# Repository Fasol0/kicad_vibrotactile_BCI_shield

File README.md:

## Printed Circuit board (PCB) settings:

- Dimensions  : 99.06mm x 53.34mm
- Material    : FR-4 TG130
- Layers      : 2
- Thickness   : 1.6mm
- Solder Mask : Green
- Silkscreen  : White
- Finish      : HASL/ENIG
- Vias        : Tenting vias
- Copper      : 1 oz. (All layers) 

### List of some manufacturers:
- PCBGoGo
- UET PCB
- SeeedStudio
- JLCPCB

### HOW TO ORDER:

Go to one of these manufacturers website, then:

#### OPTION 1 - FULL ASSEMBLED BOARD (PCBA):

- Select PCBA (PCB + Assembly) option
- Fill PCB settings
- upload Manufacturing_PCBA.zip

#### OPTION 2 - PCB Only, hand soldering:

- Select PCB option
- Fill PCB settings
- upload Manufacturing_PCB.zip
- buy all components in the BOM_PartType-Vibrotactile BCI shield.xlsx file

these components can be bought from several distributors:
Farnell, RScomponents, Digikey, Mouser, Arrow..

### Note:
N-MOSFETs are often facing shortages. 
if BS170 is not available, it can be replaced by one of these references:
- 2N7000
- BS270
- VN2106N3-G
- VN10KN3-G
- 2N7008-G
- TN2106N3-G
- TN5325N3-G
- ZVN2110A

---

## MOTORS:

2 options:

Fast delivery (1-3 days) :
https://www.amazon.fr/0-3in-moteur-vibration-%C3%A9tanche-masseur/dp/B08CHHMVWY/ref=sr_1_4?crid=2JJ113Z7XVKXU&keywords=moteur+vibrant+7mm&qid=1655198366&s=industrial&sprefix=moteur+vibrant+7mm%2Cindustrial%2C63&sr=1-4

Lowest price (1-2 months) : select the 1.5V to 3.7V version
https://fr.aliexpress.com/item/1005002945728204.html?spm=a2g0o.productlist.0.0.43501c7ajrwj7v&algo_pvid=59802b58-b0c1-436a-8371-263ce5a04aeb&algo_exp_id=59802b58-b0c1-436a-8371-263ce5a04aeb-2&pdp_ext_f=%7B%22sku_id%22%3A%2212000022908295436%22%7D&pdp_npi=2%40dis%21EUR%21%212.32%21%21%212.06%21%21%402100bdd716551982956516490e7309%2112000022908295436%21sea

### Note: 
Picking 1.5V to 5V motors instead would allow a wider vibration range and remove the need of using resistors R1 to R12.
In this case PCB should be updated to remove the resistors slots.
However these motors have higher price (2.32€ vs 1.07€ for the 3.7V version), and are harder to find for fast delivery.

---

## Updates from initial version:

- Changed software from Altium to Kicad (ver. 6)
- PCB dimensions reduced to 99.00 x 53.34mm
- obsolete MOSFET BS170G replaced by BS170
- Motor connectors reference replaced to 282834-2 (smaller footprint, and higher availability)
- Resistors R1 to R12 changed from 6.8 Ohm to 24 Ohm

Motors are rated 3.0V and can go up to 3.7V.  
Current at 3.7V is about 55mA.  
Motors are powered with the 5V rail from the Arduino. Since motors voltage should not exceed 3.7V,  
Resistors R1 to R12 values should be:  
R = DV / I with:  
DV = 5-3.7V = 1.3V  
I = 55mA  
Therefore R = 24 Ohm  

With this setup all motors can safely be driven by PWM from 0 to 100% dutycycle.

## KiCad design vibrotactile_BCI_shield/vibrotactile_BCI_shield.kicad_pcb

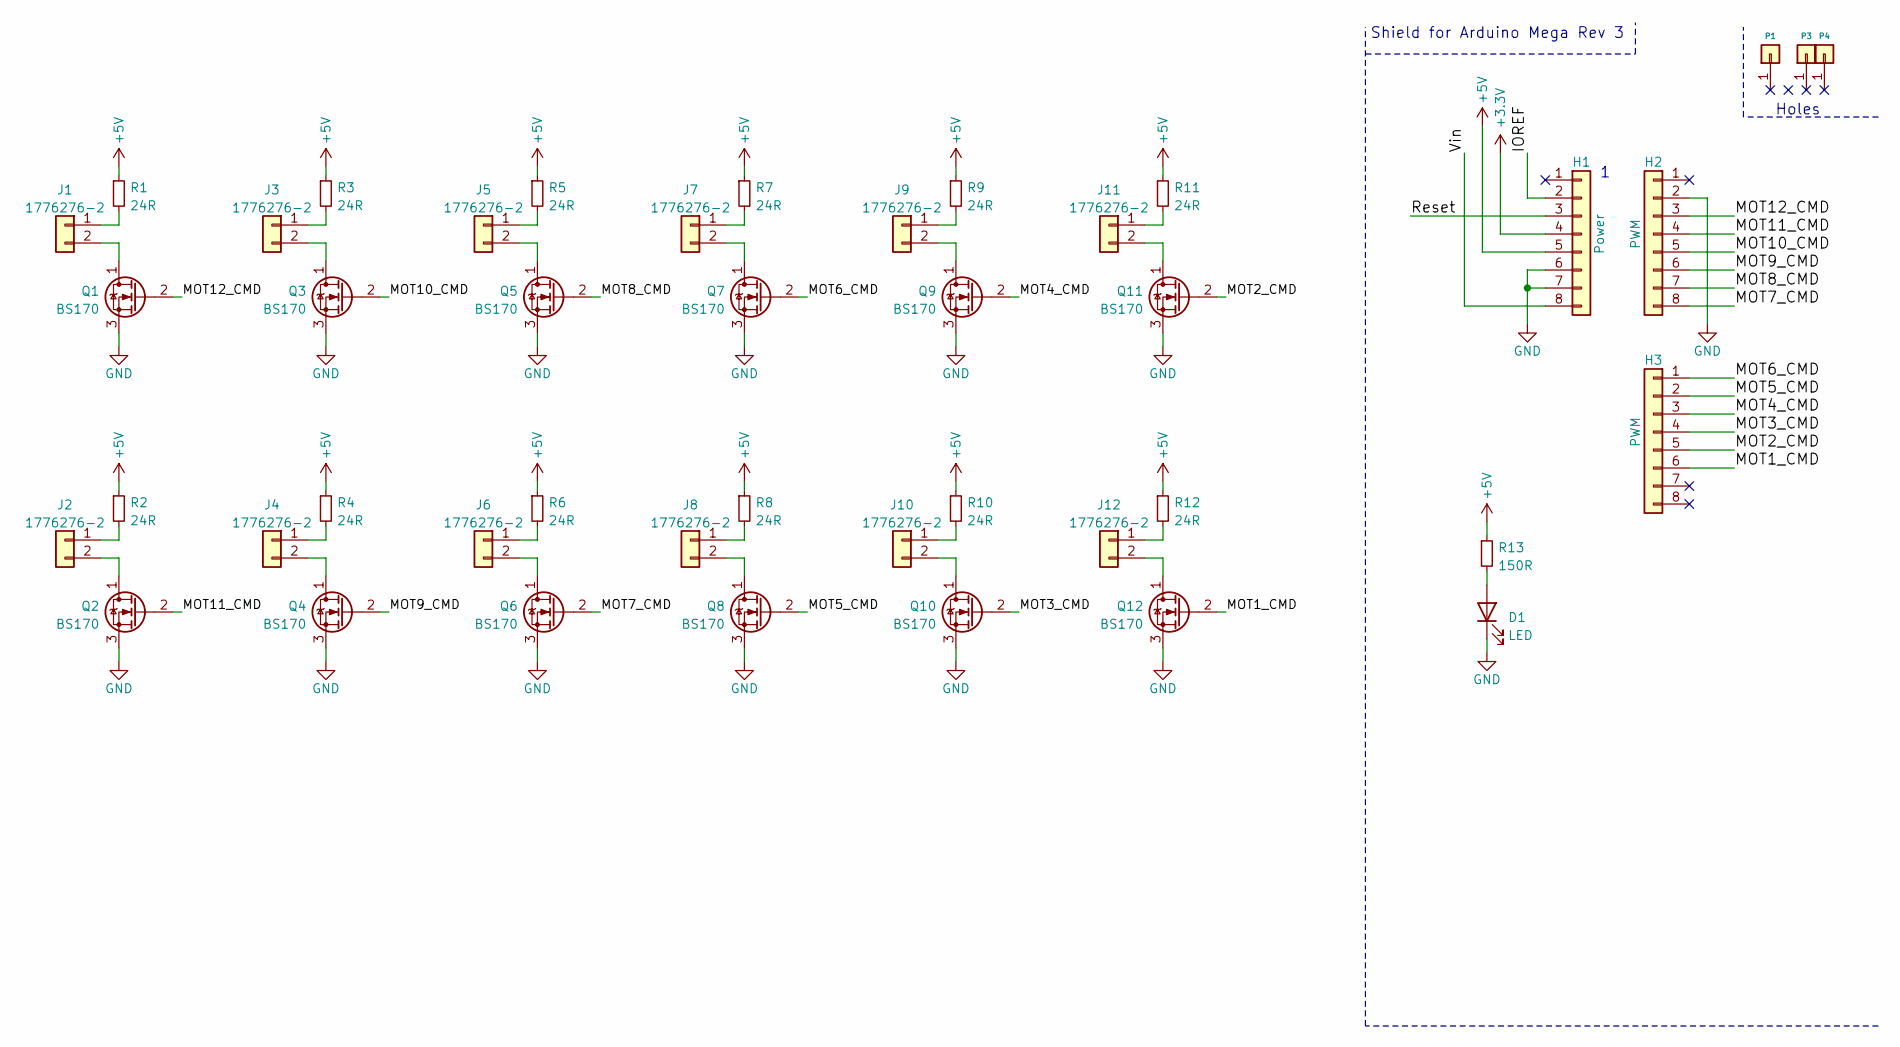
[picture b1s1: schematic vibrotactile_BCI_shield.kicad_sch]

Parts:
D1: LED; LED_D3.0mm
H1: Power; Socket_Strip_Arduino_1x08
H2, H3: PWM; Socket_Strip_Arduino_1x08
J1, J2, J3, J4, J5, J6, J7, J8, J9, J10, J11, J12: 1776276-2; TE_Connectivity282834-2
P1, P3, P4: CONN_01X01; Arduino_1pin
Q1, Q2, Q3, Q4, Q5, Q6, Q7, Q8, Q9, Q10, Q11, Q12: BS170; TO-92_Inline
R1, R2, R3, R4, R5, R6, R7, R8, R9, R10, R11, R12: 24R; R_Axial_DIN0207_L6.3mm_D2.5mm_P10.16mm_Horizontal
R13: 150R; R_Axial_DIN0207_L6.3mm_D2.5mm_P10.16mm_Horizontal

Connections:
+3V3: H1.4
+5V: H1.5, R1.1, R2.1, R3.1, R4.1, R5.1, R6.1, R7.1, R8.1, R9.1, R10.1, R11.1, R12.1, R13.1
/IOREF: H1.2
/MOT1_CMD: H3.6, Q12.2 (G)
/MOT2_CMD: H3.5, Q11.2 (G)
/MOT3_CMD: H3.4, Q10.2 (G)
/MOT4_CMD: H3.3, Q9.2 (G)
/MOT5_CMD: H3.2, Q8.2 (G)
/MOT6_CMD: H3.1, Q7.2 (G)
/MOT7_CMD: H2.8, Q6.2 (G)
/MOT8_CMD: H2.7, Q5.2 (G)
/MOT9_CMD: H2.6, Q4.2 (G)
/MOT10_CMD: H2.5, Q3.2 (G)
/MOT11_CMD: H2.4, Q2.2 (G)
/MOT12_CMD: H2.3, Q1.2 (G)
/Reset: H1.3
/Vin: H1.8
GND: D1.1 (K), H1.6, H1.7, H2.2, Q1.3 (S), Q2.3 (S), Q3.3 (S), Q4.3 (S), Q5.3 (S), Q6.3 (S), Q7.3 (S), Q8.3 (S), Q9.3 (S), Q10.3 (S), Q11.3 (S), Q12.3 (S)
unnamed: D1.2 (A), R13.2
unnamed: J1.1, R1.2
unnamed: J1.2, Q1.1 (D)
unnamed: J2.1, R2.2
unnamed: J2.2, Q2.1 (D)
unnamed: J3.1, R3.2
unnamed: J3.2, Q3.1 (D)
unnamed: J4.1, R4.2
unnamed: J4.2, Q4.1 (D)
unnamed: J5.1, R5.2
unnamed: J5.2, Q5.1 (D)
unnamed: J6.1, R6.2
unnamed: J6.2, Q6.1 (D)
unnamed: J7.1, R7.2
unnamed: J7.2, Q7.1 (D)
unnamed: J8.1, R8.2
unnamed: J8.2, Q8.1 (D)
unnamed: J9.1, R9.2
unnamed: J9.2, Q9.1 (D)
unnamed: J10.1, R10.2
unnamed: J10.2, Q10.1 (D)
unnamed: J11.1, R11.2
unnamed: J11.2, Q11.1 (D)
unnamed: J12.1, R12.2
unnamed: J12.2, Q12.1 (D)

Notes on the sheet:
Holes
Shield for Arduino Mega Rev 3

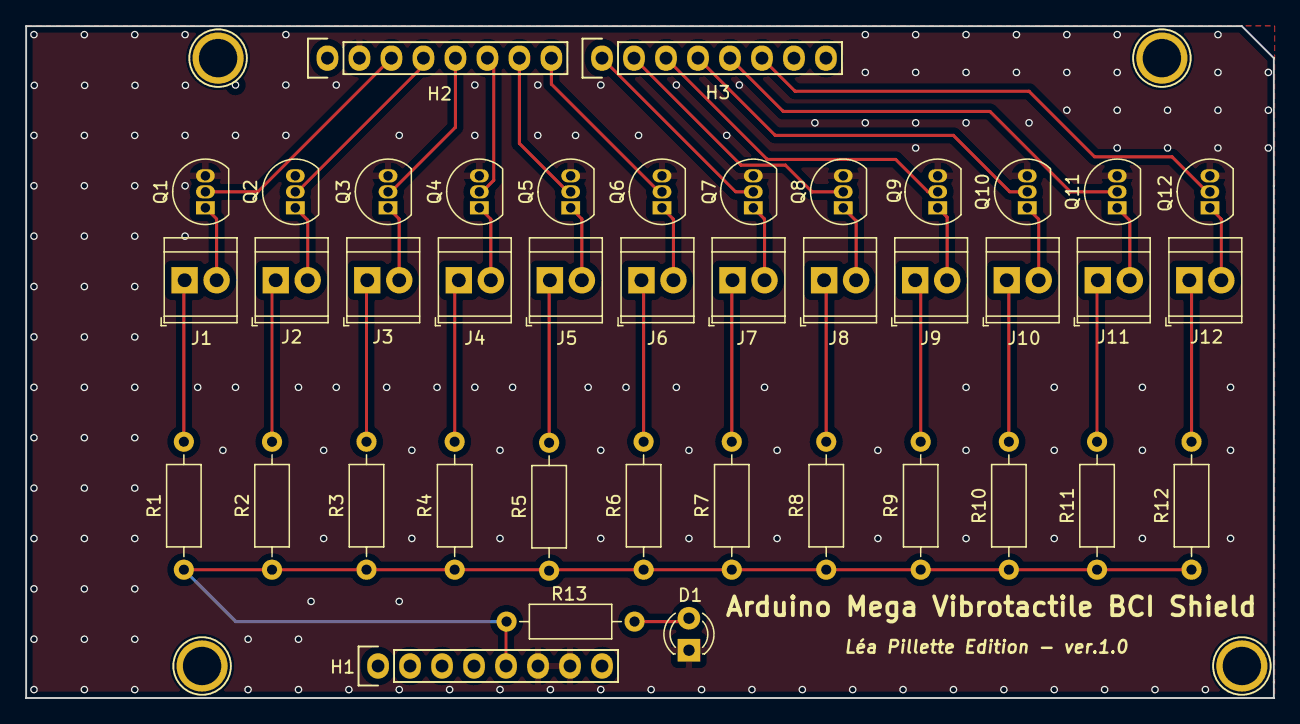
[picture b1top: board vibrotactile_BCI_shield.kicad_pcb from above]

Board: 2 copper layers, 99.1 x 53.3 mm, 45 parts (0 on the bottom side), 39 nets.

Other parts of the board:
P2: CONN_01X01; Arduino_1pin

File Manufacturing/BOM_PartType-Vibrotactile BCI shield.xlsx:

Designator | Description | Manufacturer Part Number | Manufacturer | Quantity | Octopart URL
H1, H2, H3 | Conn Unshrouded Header HDR 8 POS 2.54mm Solder ST Thru-Hole Automotive Bulk | TSW-108-15-L-S | Samtec | 3 | http://octopart.com/tsw-108-15-l-s-samtec-11810720
D1 | Grn diffused reflector LED, L1334GT 25mA | L-1334GT | Kingbright | 1 | http://octopart.com/l-1334gt-kingbright-55391525
Q1, Q2, Q3, Q4, Q5, Q6, Q6, Q7, Q8, Q9, Q10, Q11, Q12 | Small Signal MOSFET, 500 mA, 60 V, N-Channel, 3-Pin TO-92, Pb-Free, Bulk Box | BS170 | OnSemi | 12 | https://octopart.com/search?q=BS170&currency=USD&specs=0
M1, M2, M3, M4, M5, M6, M7, M8, M9, M10, M11, M12 | Wire to Board 2 Position 2.54 mm Pitch 30-16 AWG Terminal Block | 282834-2 | TE Connectivity | 12 | https://octopart.com/search?q=282834-2&currency=USD&specs=0
R13 | Metal Film Resistors 150 Ohm 3/5W 50PPM | LR1F150R | TE Connectivity | 1 | https://octopart.com/search?autosugg_idx=0&currency=USD&oq=L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
R1, R2, R3, R4, R5, R6, R7, R8, R9, R10, R11, R12 | Metal Film Resistors 24 Ohm 3/5W 50PPM | LR1F24R | TE Connectivity | 12 | https://octopart.com/search?autosugg_idx=0&currency=USD&oq=L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

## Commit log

2022-06-14 prod files
2022-06-15 alternative headers
2022-06-15 adding farnell ref
2022-06-20 adding missing gerbers
2022-06-20 updating archives
